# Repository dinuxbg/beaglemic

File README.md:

# BeagleMic 16-channel PDM Audio Capture

# Introduction
Ever wanted to record audio from 16 PDM microphones simultanously? Now you can with a BeagleMic running on a [PocketBeagle2](https://www.beagleboard.org/boards/pocketbeagle-2).

Yes, you could opt for the much simpler I2S microphones. But then you won't have fun writing assembly to capture and process sixteen digital signals at more than 2MHz sample rate.

Audio can be routed to BeagleBone's USB gadget driver. Multichannel audio data can be recorded from a regular PC just as you would record from any other USB microphone. See the section about Buildroot image below.

Current firmware supports:

| Feature                    | 16 Channel Mode   | 8 Channel Mode    |
|----------------------------|-------------------|-------------------|
| PDM Bit Clock              | 3.083 MHz         | 3,083 MHz         |
| PCM Output Bits Per Sample | 16 bps            | 24 bps            |
| PCM Output Sample Rate     | 24088 Samples/sec | 24088 Samples/sec |

# Freedom
To the best of my knowledge, the entire HW design is Open Hardware and designed with the libre KiCad software. The entire firmware stack is almost free software, and is built by free toolchains. The only exception are some bootloader blobs for the AM62x SoC.

Please report any closed components you notice.

# Hardware
The schematic is simple. PDM microphones' digital outputs are connected directly to the PRU input pins. The PRU also drives the bit clock. I have tested on PocketBeagle and BeagleBone AI.

| PocketBeagle | PRU Pin | Type  | Signal               |
|--------------|---------|-------|----------------------|
| P2.24        | R30_14  | Output| PDM Bit Clock        |
| P1.36        | R31_0   | Input | MIC0 and MIC1 Data   |
| P1.33        | R31_1   | Input | MIC2 and MIC3 Data   |
| P2.32        | R31_2   | Input | MIC4 and MIC5 Data   |
| P2.30        | R31_3   | Input | MIC6 and MIC7 Data   |
| P1.31        | R31_4   | Input | MIC8 and MIC9 Data   |
| P2.34        | R31_5   | Input | MIC10 and MIC11 Data |
| P2.28        | R31_6   | Input | MIC12 and MIC13 Data |
| P1.29        | R31_7   | Input | MIC14 and MIC15 Data |

Optionally, high-level software may visualize detected audio direction using a stripe of 16 LEDs hooked to two 74HC595 shift registers:

| PocketBeagle | PB GPIO  | BBAI  | BBAI GPIO | Signal |
|--------------|----------|-------|-----------|--------|
| P2.25        | gpio2_9  | P9.30 | gpio5_12  | DS     |
| P2.29        | gpio1_7  | P9.28 | gpio4_17  | SHCP   |
| P2.31        | gpio1_19 | P9.23 | gpio7_11  | STCP   |

For each microphone pair, one microphone is configured to output data on the rising clock edge, and the other is configured to output data on the falling edge. This way we need only 8 input GPIOs to capture data from all 16 microphones.

Microphone breakout board and a PocketBeagle2 Cape are provided in KiCad format.

Unfortunately the breakout board is essential for a home DIY user like me, since all PDM microphones I could find are BGA. There are numerous youtube guides how to solder BGAs at home using a skillet or a toaster oven.

# Software

PRU0 takes care of driving the PDM bit clock and capturing the microphone bit data. It then runs a CIC filter to convert PDM to PCM, and feeds PCM data to PRU1.

PRU0 has two alternative modes of operation. For 16 channels it executes 2 integrator and 2 comb stages for CIC filtering. Whereas for 8 channels it does 3.

PRU1 is retransmitting PCM data from PRU0 down to the ARM host. RPMSG is used for control commands. Shared DDRAM buffers are used for audio data.

Host audio driver presents a standard ALSA audio card, so that arecord and other standard tools can be readily used.

# Running The Example on PocketBeagle2

    # Build kernel module
    sudo apt update
    sudo apt install build-essential linux-headers-`uname -r`
    cd driver
    make
    # Install kernel module
    sudo cp beaglemic.ko /lib/modules/`uname -r`/kernel/drivers/rpmsg/
    sudo depmod -a

    # Load the driver
    sudo modprobe beaglemic

    # Build PRU firmware
    cd pru
    make
    # Start the new PRU firmware
    sudo ./start.sh

    # Record audio
    arecord  -r31888  -c16 -f S16_LE -t wav out.wav
    arecord  -r26940  -c8 -f S32_LE -t wav out.wav
    # Hit Ctrl+C to stop.

# Folder Structure

 * beaglemic-cape - Universal cape for BeagleBone AI, PocketBeagle, PocketBeagle2 and iCE40HX8K-EVB.
 * driver - Host ALSA audio driver.
 * inmp621-breakout - INMP621 Microphone breakout. Designed to be optionally used with beaglemic-cape.
 * libs - Library code. Currently contains code to drive LED ring for beaglemic-cape.
 * pru - PRU firmware.

# Further Work
A few ideas to improve the design:

 * Move comb filters to PRU1, and try to add more integrators in PRU0.
 * Clean-up the cape PCB.
   * If possible, leave headers for Class-D output from spare PRUs.
 * Migrate to latest kernel 6.??.

# Buildroot Image With USB UAC2 Gadget Mode
The above installation and build instruction steps can be daunting. A [buildroot](https://buildroot.org) configuration for PocketBeagle2 is available to automate them, and add a bit more.

The buildroot image is small (about 6MB). It initializes the BeagleMic audio driver, and links it to the UAC2 USB Gadget driver. Your BeagleMic PocketBeagle2 is presented as USB multichannel microphone, so that a regular PC can capture and run desired audio algorithms.

You need to download the beaglemic and buildroot.org GIT trees in separate directories. Then, when building from the buildroot directory you need to provide the beaglemic path via BR2_EXTERNAL environment variable. Example commands:

	git clone --depth=1 git://git.busybox.net/buildroot
	git clone --depth=1 https://gitlab.com/dinuxbg/beaglemic

	cd buildroot
	git checkout 2021.05.3  # Last BR release with kernel 4.19
	export BR2_EXTERNAL=`realpath ../beaglemic/buildroot/`
	make beaglemic_pb2_defconfig
	make -j`nproc`

Above should result in a small SDCard image which you can flash. Be sure to get the /dev/sdX right for your SD/MMC card reader.

	sudo dd if=output/images/sdcard.img of=/dev/sdX

When PocketBeagle2 boots and you connect it via USB to your host, you should be able to record:

	arecord -D hw:CARD=BeagleMic -c8 -t wav -f S32_LE -r24000 out-8ch.wav

## Audio Mode Configuration
Right now UAC2 Gadget is configured only for 8ch/32bps/24000kHz. With a few manual tweaks in buildroot/package/beaglemic-firmware/beaglemicd it can be switched to 16ch/16bps mode. I'm currently researching how I can make this configuration run-time, and how I can control the LED ring via USB.

# References
 * [CIC Filter Introduction](https://dspguru.com/dsp/tutorials/cic-filter-introduction/)
 * [Another CIC Filter Article](http://www.tsdconseil.fr/log/scriptscilab/cic/cic-en.pdf)
 * [Series of PDM articles and software implementations](https://curiouser.cheshireeng.com/category/projects/pdm-microphone-toys/)
 * [Another CIC Filter Article](https://www.embedded.com/design/configurable-systems/4006446/Understanding-cascaded-integrator-comb-filters)
 * [CIC Filter Introduction](http://home.mit.bme.hu/~kollar/papers/cic.pdf)
 * [SPM0423HD4H Datasheet](http://media.digikey.com/PDF/Data%20Sheets/Knowles%20Acoustics%20PDFs/SPM0423HD4H-WB.pdf)
 * [INMP621 Datasheet](https://invensense.tdk.com/download-pdf/inmp621-datasheet/)
 * [Inspiration for high-bandwidth data acquisition](https://github.com/ZeekHuge/BeagleScope)

# Other Resources
Below are various other CIC implementations and PDM microphone boards I've stumbled upon.
 * https://github.com/introlab/16SoundsUSB
 * https://github.com/mkj/pru-mic
 * https://github.com/introlab/odas
 * https://respeaker.io/make_a_smart_speaker/
 * https://github.com/Scrashdown/PRU-Audio-Processing
 * https://github.com/fakufaku/kurodako

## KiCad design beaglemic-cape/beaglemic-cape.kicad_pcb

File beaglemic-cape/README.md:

# Beaglemic-Cape

This is a KiCAD project for a 16 PDM Microphone board with host support for:
 * BeagleBone AI
 * PocketBeagle
 * ICE40HX8K-EVB1 (**untested!**)

PDM microphones can either be:
 * Soldered on the cape board, which is not for beginners. You would require a steady hand or pick-and-place machine, and reflow soldering oven.
 * Connected via regular headers using external [breakout](../inmp621-breakout/README.md) [board](https://www.adafruit.com/product/3492).

# Future Improvements

A few ideas for improvements in an eventual future PCB revision:

 * Move the USB OTG connector to the outer edge, so that cable does not interfere with PocketBeagle.
 * Add a few extra LEDs for power and other status.
 * Add better package placement indicators on silkscreen (e.g. first pin, IC dent).
 * Remove the BBAI connector. I couldn't find a way to utilize the proprietary DSPs, so let's focus on USB microphone with PocketBeagle.
 * Switch to bottom-facing LEDs so that all SMD parts are on one of the PCB sides.

# References
 * Microphone footprint, 3D model and schematics symbol are taken from https://www.snapeda.com/parts/INMP621/InvenSense/view-part/?ref=digikey . Footprint has minor modification to "break" the ground track and ease the data wires routing.
 * Freerouting.org was used for routing some of the PCB tracks.

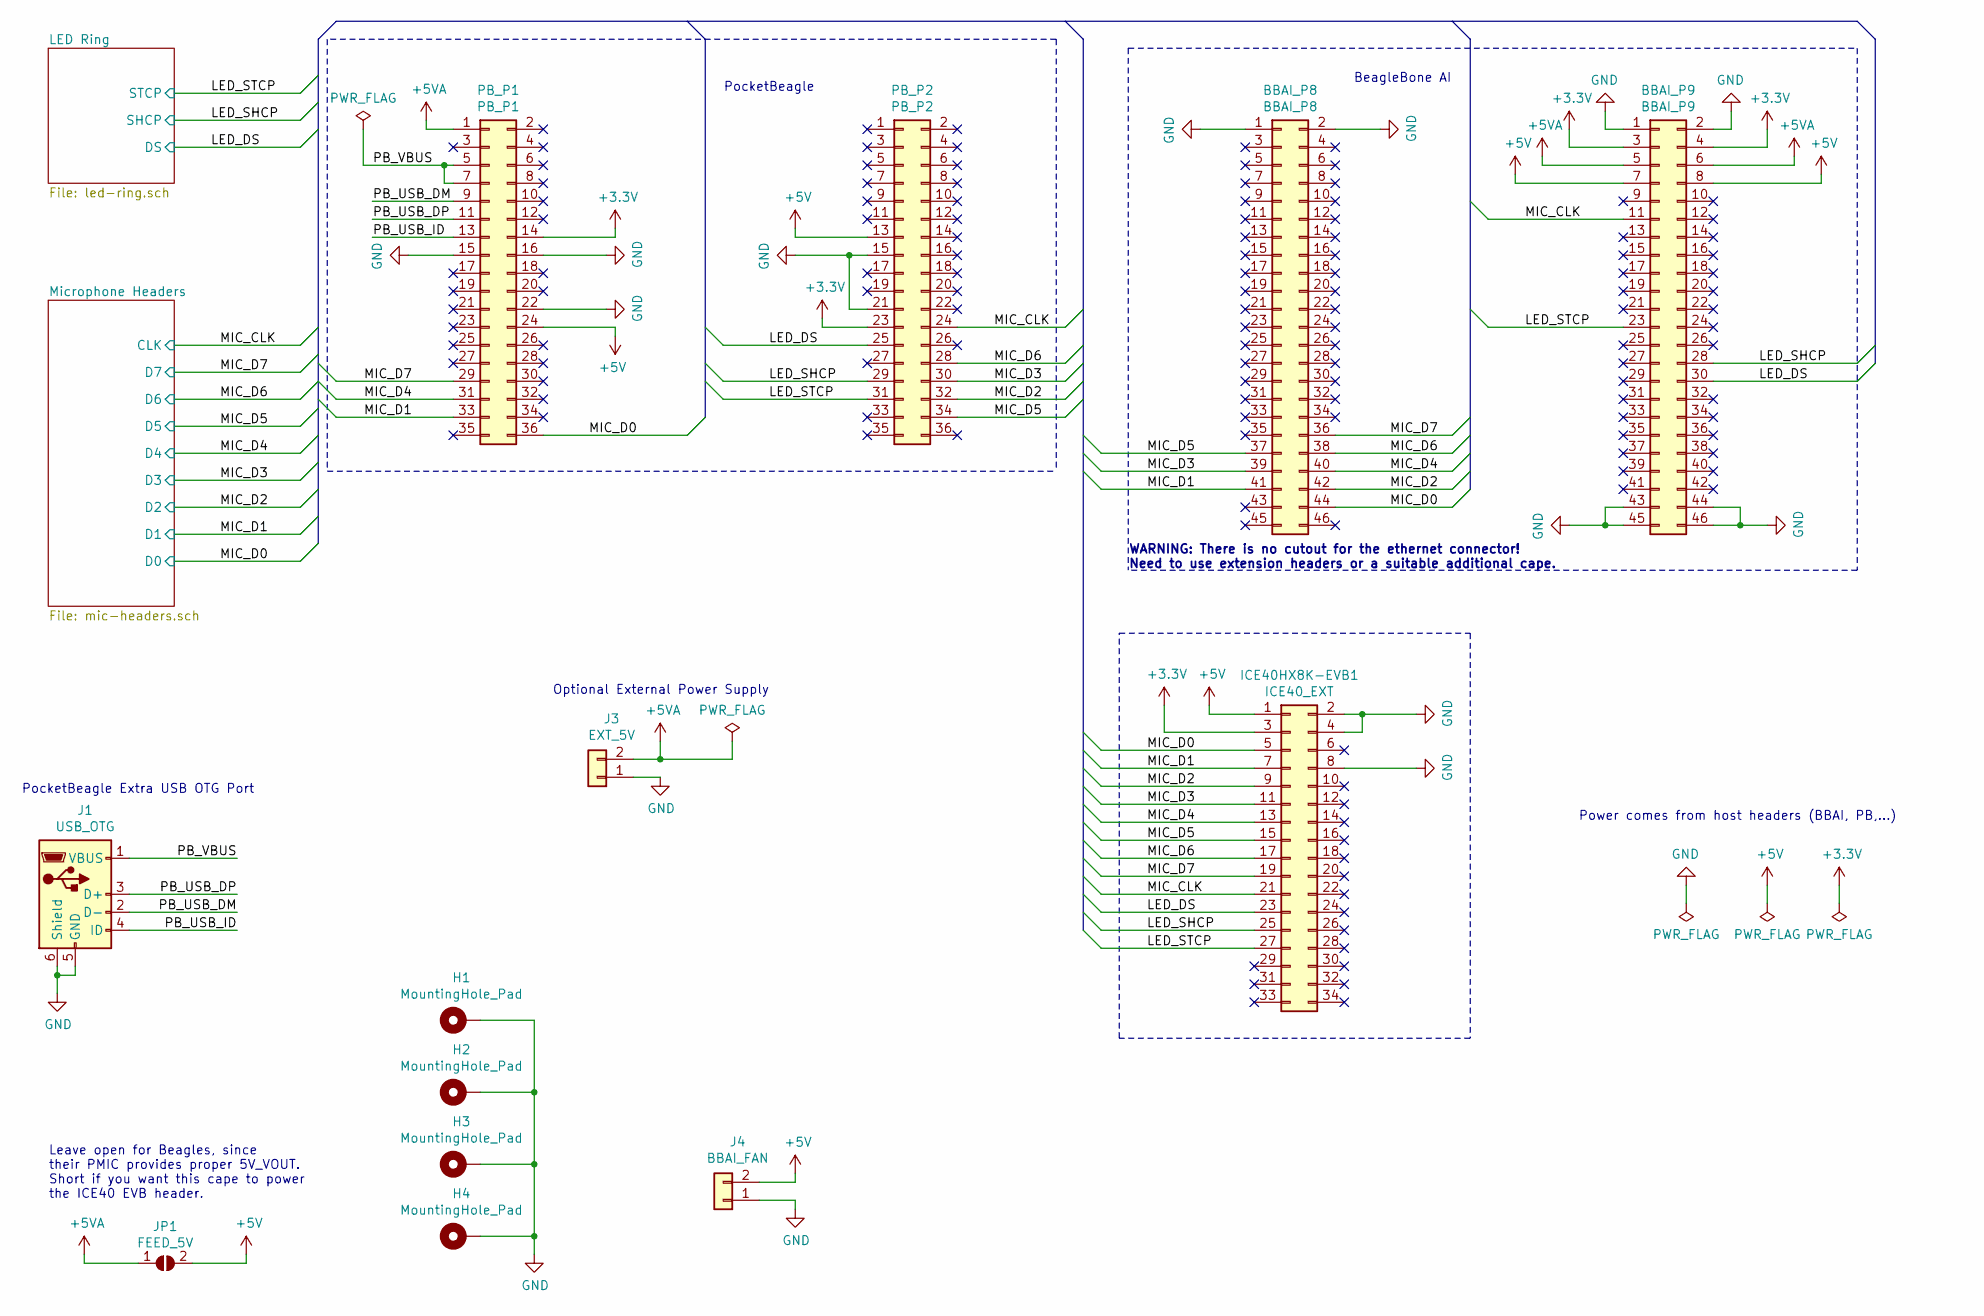
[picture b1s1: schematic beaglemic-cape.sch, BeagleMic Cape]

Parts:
BBAI_P8: BBAI_P8; PinSocket_2x23_P2.54mm_Vertical
BBAI_P9: BBAI_P9; PinSocket_2x23_P2.54mm_Vertical
H1, H2, H3, H4: MountingHole_Pad; MountingHole_3.2mm_M3_ISO14580_Pad
ICE40HX8K-EVB1: ICE40_EXT; PinSocket_2x17_P2.54mm_Vertical
J1: USB_OTG; USB_Micro-B_Tensility_54-00023_Vertical_CircularHoles
J3: EXT_5V; PinHeader_1x02_P2.54mm_Vertical
J4: BBAI_FAN; PinHeader_1x02_P2.54mm_Vertical
JP1: FEED_5V; SolderJumper-2_P1.3mm_Open_RoundedPad1.0x1.5mm
PB_P1: PB_P1; PinHeader_2x18_P2.54mm_Vertical
PB_P2: PB_P2; PinHeader_2x18_P2.54mm_Vertical

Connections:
+3V3: BBAI_P9.3, BBAI_P9.4, ICE40HX8K-EVB1.3, PB_P1.14, PB_P2.23; also elsewhere on the board
+5V: BBAI_P9.7, BBAI_P9.8, ICE40HX8K-EVB1.1, J4.2, JP1.2 (B), PB_P1.24, PB_P2.13; also elsewhere on the board
+5VA: BBAI_P9.5, BBAI_P9.6, J3.2, JP1.1 (A), PB_P1.1
/LED_DS: BBAI_P9.30, ICE40HX8K-EVB1.23, PB_P2.25; also elsewhere on the board
/LED_SHCP: BBAI_P9.28, ICE40HX8K-EVB1.25, PB_P2.29; also elsewhere on the board
/LED_STCP: BBAI_P9.23, ICE40HX8K-EVB1.27, PB_P2.31; also elsewhere on the board
/MIC_CLK: BBAI_P9.11, ICE40HX8K-EVB1.21, PB_P2.24; also elsewhere on the board
/MIC_D0: BBAI_P8.44, ICE40HX8K-EVB1.5, PB_P1.36; also elsewhere on the board
/MIC_D1: BBAI_P8.41, ICE40HX8K-EVB1.7, PB_P1.33; also elsewhere on the board
/MIC_D2: BBAI_P8.42, ICE40HX8K-EVB1.9, PB_P2.32; also elsewhere on the board
/MIC_D3: BBAI_P8.39, ICE40HX8K-EVB1.11, PB_P2.30; also elsewhere on the board
/MIC_D4: BBAI_P8.40, ICE40HX8K-EVB1.13, PB_P1.31; also elsewhere on the board
/MIC_D5: BBAI_P8.37, ICE40HX8K-EVB1.15, PB_P2.34; also elsewhere on the board
/MIC_D6: BBAI_P8.38, ICE40HX8K-EVB1.17, PB_P2.28; also elsewhere on the board
/MIC_D7: BBAI_P8.36, ICE40HX8K-EVB1.19, PB_P1.29; also elsewhere on the board
/PB_USB_DM: J1.2 (D-), PB_P1.9
/PB_USB_DP: J1.3 (D+), PB_P1.11
/PB_USB_ID: J1.4 (ID), PB_P1.13
/PB_VBUS: J1.1 (VBUS), PB_P1.5, PB_P1.7
GND: BBAI_P8.1, BBAI_P8.2, BBAI_P9.1, BBAI_P9.2, BBAI_P9.43, BBAI_P9.44, BBAI_P9.45, BBAI_P9.46, H1.1, H2.1, H3.1, H4.1, ICE40HX8K-EVB1.2, ICE40HX8K-EVB1.4, ICE40HX8K-EVB1.8, J1.5 (GND), J1.6 (Shield), J3.1, J4.1, PB_P1.15, PB_P1.16, PB_P1.22, PB_P2.15, PB_P2.21; also elsewhere on the board

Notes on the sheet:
Power comes from host headers (BBAI, PB,...)
PocketBeagle Extra USB OTG Port
Optional External Power Supply
Leave open for Beagles, since their PMIC provides proper 5V_VOUT. Short if you want this cape to power the ICE40 EVB header.
PocketBeagle
BeagleBone AI
WARNING: There is no cutout for the ethernet connector! Need to use extension headers or a suitable additional cape.

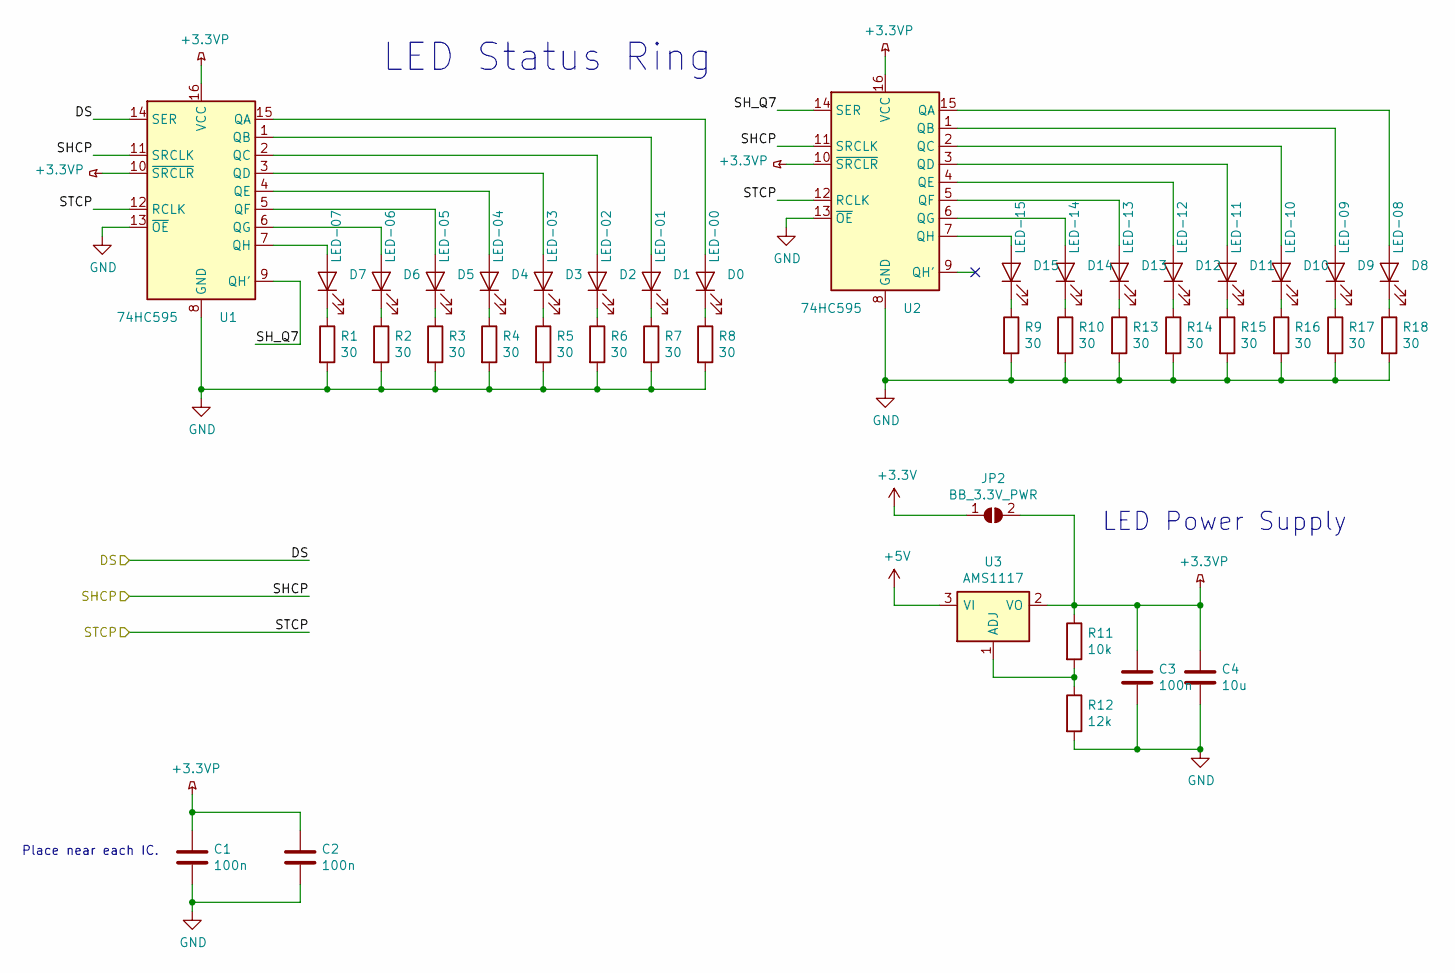
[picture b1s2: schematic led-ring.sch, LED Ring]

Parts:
C1, C2, C3: 100n; C_0805_2012Metric
C4: 10u; C_0805_2012Metric
D0: LED-00; LED_0805_2012Metric
D1: LED-01; LED_0805_2012Metric
D2: LED-02; LED_0805_2012Metric
D3: LED-03; LED_0805_2012Metric
D4: LED-04; LED_0805_2012Metric
D5: LED-05; LED_0805_2012Metric
D6: LED-06; LED_0805_2012Metric
D7: LED-07; LED_0805_2012Metric
D8: LED-08; LED_0805_2012Metric
D9: LED-09; LED_0805_2012Metric
D10: LED-10; LED_0805_2012Metric
D11: LED-11; LED_0805_2012Metric
D12: LED-12; LED_0805_2012Metric
D13: LED-13; LED_0805_2012Metric
D14: LED-14; LED_0805_2012Metric
D15: LED-15; LED_0805_2012Metric
JP2: BB_3.3V_PWR; SolderJumper-2_P1.3mm_Open_RoundedPad1.0x1.5mm
R1, R2, R3, R4, R5, R6, R7, R8, R9, R10, R13, R14, R15, R16, R17, R18: 30; R_0805_2012Metric
R11: 10k; R_0805_2012Metric
R12: 12k; R_0805_2012Metric
U1, U2: 74HC595; TSSOP-16_4.4x5mm_P0.65mm
U3: AMS1117; SOT-223-3_TabPin2

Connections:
+3.3VP: C1.1, C2.1, C3.1, C4.1, JP2.2 (B), R11.1, U1.10 (~SRCLR), U1.16 (VCC), U2.10 (~SRCLR), U2.16 (VCC), U3.2 (VO)
+3V3: JP2.1 (A); also elsewhere on the board
+5V: U3.3 (VI); also elsewhere on the board
/LED Ring/SH_Q7: U1.9 (QH'), U2.14 (SER)
/LED_DS: U1.14 (SER); also elsewhere on the board
/LED_SHCP: U1.11 (SRCLK), U2.11 (SRCLK); also elsewhere on the board
/LED_STCP: U1.12 (RCLK), U2.12 (RCLK); also elsewhere on the board
GND: C1.2, C2.2, C3.2, C4.2, R1.2, R2.2, R3.2, R4.2, R5.2, R6.2, R7.2, R8.2, R9.2, R10.2, R12.2, R13.2, R14.2, R15.2, R16.2, R17.2, R18.2, U1.8 (GND), U1.13 (~OE), U2.8 (GND), U2.13 (~OE); also elsewhere on the board
unnamed: D0.1 (K), R8.1
unnamed: D0.2 (A), U1.15 (QA)
unnamed: D1.1 (K), R7.1
unnamed: D1.2 (A), U1.1 (QB)
unnamed: D2.1 (K), R6.1
unnamed: D2.2 (A), U1.2 (QC)
unnamed: D3.1 (K), R5.1
unnamed: D3.2 (A), U1.3 (QD)
unnamed: D4.1 (K), R4.1
unnamed: D4.2 (A), U1.4 (QE)
unnamed: D5.1 (K), R3.1
unnamed: D5.2 (A), U1.5 (QF)
unnamed: D6.1 (K), R2.1
unnamed: D6.2 (A), U1.6 (QG)
unnamed: D7.1 (K), R1.1
unnamed: D7.2 (A), U1.7 (QH)
unnamed: D8.1 (K), R18.1
unnamed: D8.2 (A), U2.15 (QA)
unnamed: D9.1 (K), R17.1
unnamed: D9.2 (A), U2.1 (QB)
unnamed: D10.1 (K), R16.1
unnamed: D10.2 (A), U2.2 (QC)
unnamed: D11.1 (K), R15.1
unnamed: D11.2 (A), U2.3 (QD)
unnamed: D12.1 (K), R14.1
unnamed: D12.2 (A), U2.4 (QE)
unnamed: D13.1 (K), R13.1
unnamed: D13.2 (A), U2.5 (QF)
unnamed: D14.1 (K), R10.1
unnamed: D14.2 (A), U2.6 (QG)
unnamed: D15.1 (K), R9.1
unnamed: D15.2 (A), U2.7 (QH)
unnamed: R11.2, R12.1, U3.1 (ADJ)

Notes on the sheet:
LED Status Ring
LED Power Supply
Place near each IC.

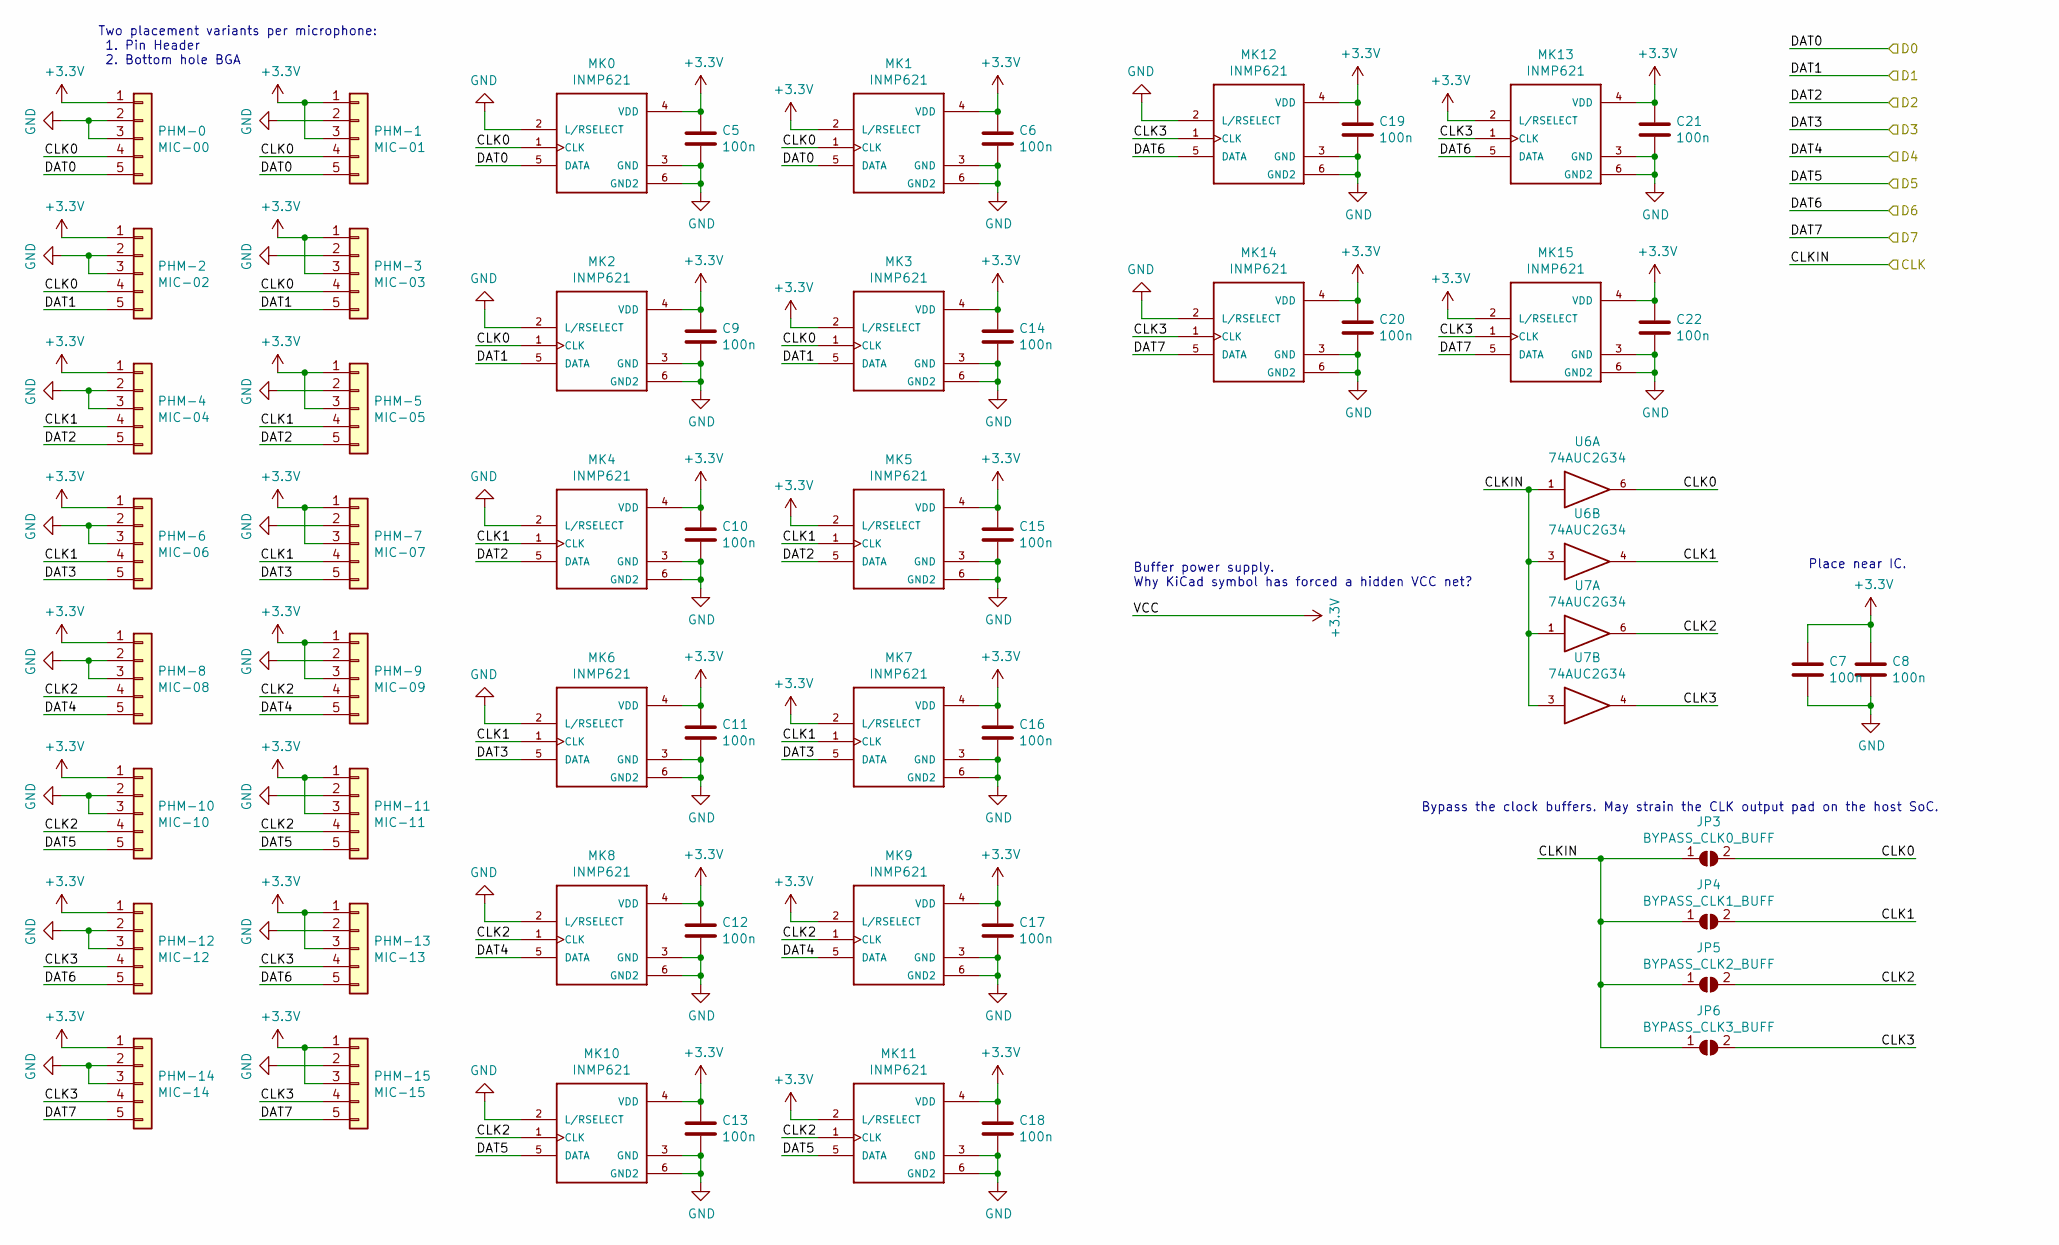
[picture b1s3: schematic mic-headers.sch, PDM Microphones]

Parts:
C5, C6, C7, C8, C9, C10, C11, C12, C13, C14, C15, C16, C17, C18, C19, C20, C21, C22: 100n; C_0805_2012Metric
JP3: BYPASS_CLK0_BUFF; SolderJumper-2_P1.3mm_Open_RoundedPad1.0x1.5mm
JP4: BYPASS_CLK1_BUFF; SolderJumper-2_P1.3mm_Open_RoundedPad1.0x1.5mm
JP5: BYPASS_CLK2_BUFF; SolderJumper-2_P1.3mm_Open_RoundedPad1.0x1.5mm
JP6: BYPASS_CLK3_BUFF; SolderJumper-2_P1.3mm_Open_RoundedPad1.0x1.5mm
MK0, MK1, MK2, MK3, MK4, MK5, MK6, MK7, MK8, MK9, MK10, MK11, MK12, MK13, MK14, MK15: INMP621; MK_INMP621
PHM-0: MIC-00; PinSocket_1x05_P2.54mm_Vertical
PHM-1: MIC-01; PinSocket_1x05_P2.54mm_Vertical
PHM-2: MIC-02; PinSocket_1x05_P2.54mm_Vertical
PHM-3: MIC-03; PinSocket_1x05_P2.54mm_Vertical
PHM-4: MIC-04; PinSocket_1x05_P2.54mm_Vertical
PHM-5: MIC-05; PinSocket_1x05_P2.54mm_Vertical
PHM-6: MIC-06; PinSocket_1x05_P2.54mm_Vertical
PHM-7: MIC-07; PinSocket_1x05_P2.54mm_Vertical
PHM-8: MIC-08; PinSocket_1x05_P2.54mm_Vertical
PHM-9: MIC-09; PinSocket_1x05_P2.54mm_Vertical
PHM-10: MIC-10; PinSocket_1x05_P2.54mm_Vertical
PHM-11: MIC-11; PinSocket_1x05_P2.54mm_Vertical
PHM-12: MIC-12; PinSocket_1x05_P2.54mm_Vertical
PHM-13: MIC-13; PinSocket_1x05_P2.54mm_Vertical
PHM-14: MIC-14; PinSocket_1x05_P2.54mm_Vertical
PHM-15: MIC-15; PinSocket_1x05_P2.54mm_Vertical
U6, U7: 74AUC2G34; SOT-23-6

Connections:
+3V3: C5.1, C6.1, C7.1, C8.1, C9.1, C10.1, C11.1, C12.1, C13.1, C14.1, C15.1, C16.1, C17.1, C18.1, C19.1, C20.1, C21.1, C22.1, MK0.4 (VDD), MK1.2 (L/RSELECT), MK1.4 (VDD), MK2.4 (VDD), MK3.2 (L/RSELECT), MK3.4 (VDD), MK4.4 (VDD), MK5.2 (L/RSELECT), MK5.4 (VDD), MK6.4 (VDD), MK7.2 (L/RSELECT), MK7.4 (VDD), MK8.4 (VDD), MK9.2 (L/RSELECT), MK9.4 (VDD), MK10.4 (VDD), MK11.2 (L/RSELECT), MK11.4 (VDD), MK12.4 (VDD), MK13.2 (L/RSELECT), MK13.4 (VDD), MK14.4 (VDD), MK15.2 (L/RSELECT), MK15.4 (VDD), PHM-0.1, PHM-1.1, PHM-1.3, PHM-2.1, PHM-3.1, PHM-3.3, PHM-4.1, PHM-5.1, PHM-5.3, PHM-6.1, PHM-7.1, PHM-7.3, PHM-8.1, PHM-9.1, PHM-9.3, PHM-10.1, PHM-11.1, PHM-11.3, PHM-12.1, PHM-13.1, PHM-13.3, PHM-14.1, PHM-15.1, PHM-15.3, U6.5 (VCC), U7.5 (VCC); also elsewhere on the board
/MIC_CLK: JP3.1 (A), JP4.1 (A), JP5.1 (A), JP6.1 (A), U6.1, U6.3, U7.1, U7.3; also elsewhere on the board
/MIC_D0: MK0.5 (DATA), MK1.5 (DATA), PHM-0.5, PHM-1.5; also elsewhere on the board
/MIC_D1: MK2.5 (DATA), MK3.5 (DATA), PHM-2.5, PHM-3.5; also elsewhere on the board
/MIC_D2: MK4.5 (DATA), MK5.5 (DATA), PHM-4.5, PHM-5.5; also elsewhere on the board
/MIC_D3: MK6.5 (DATA), MK7.5 (DATA), PHM-6.5, PHM-7.5; also elsewhere on the board
/MIC_D4: MK8.5 (DATA), MK9.5 (DATA), PHM-8.5, PHM-9.5; also elsewhere on the board
/MIC_D5: MK10.5 (DATA), MK11.5 (DATA), PHM-10.5, PHM-11.5; also elsewhere on the board
/MIC_D6: MK12.5 (DATA), MK13.5 (DATA), PHM-12.5, PHM-13.5; also elsewhere on the board
/MIC_D7: MK14.5 (DATA), MK15.5 (DATA), PHM-14.5, PHM-15.5; also elsewhere on the board
/Microphone Headers/CLK0: JP3.2 (B), MK0.1 (CLK), MK1.1 (CLK), MK2.1 (CLK), MK3.1 (CLK), PHM-0.4, PHM-1.4, PHM-2.4, PHM-3.4, U6.6
/Microphone Headers/CLK1: JP4.2 (B), MK4.1 (CLK), MK5.1 (CLK), MK6.1 (CLK), MK7.1 (CLK), PHM-4.4, PHM-5.4, PHM-6.4, PHM-7.4, U6.4
/Microphone Headers/CLK2: JP5.2 (B), MK8.1 (CLK), MK9.1 (CLK), MK10.1 (CLK), MK11.1 (CLK), PHM-8.4, PHM-9.4, PHM-10.4, PHM-11.4, U7.6
/Microphone Headers/CLK3: JP6.2 (B), MK12.1 (CLK), MK13.1 (CLK), MK14.1 (CLK), MK15.1 (CLK), PHM-12.4, PHM-13.4, PHM-14.4, PHM-15.4, U7.4
GND: C5.2, C6.2, C7.2, C8.2, C9.2, C10.2, C11.2, C12.2, C13.2, C14.2, C15.2, C16.2, C17.2, C18.2, C19.2, C20.2, C21.2, C22.2, MK0.2 (L/RSELECT), MK0.3 (GND), MK0.6 (GND2), MK1.3 (GND), MK1.6 (GND2), MK2.2 (L/RSELECT), MK2.3 (GND), MK2.6 (GND2), MK3.3 (GND), MK3.6 (GND2), MK4.2 (L/RSELECT), MK4.3 (GND), MK4.6 (GND2), MK5.3 (GND), MK5.6 (GND2), MK6.2 (L/RSELECT), MK6.3 (GND), MK6.6 (GND2), MK7.3 (GND), MK7.6 (GND2), MK8.2 (L/RSELECT), MK8.3 (GND), MK8.6 (GND2), MK9.3 (GND), MK9.6 (GND2), MK10.2 (L/RSELECT), MK10.3 (GND), MK10.6 (GND2), MK11.3 (GND), MK11.6 (GND2), MK12.2 (L/RSELECT), MK12.3 (GND), MK12.6 (GND2), MK13.3 (GND), MK13.6 (GND2), MK14.2 (L/RSELECT), MK14.3 (GND), MK14.6 (GND2), MK15.3 (GND), MK15.6 (GND2), PHM-0.2, PHM-0.3, PHM-1.2, PHM-2.2, PHM-2.3, PHM-3.2, PHM-4.2, PHM-4.3, PHM-5.2, PHM-6.2, PHM-6.3, PHM-7.2, PHM-8.2, PHM-8.3, PHM-9.2, PHM-10.2, PHM-10.3, PHM-11.2, PHM-12.2, PHM-12.3, PHM-13.2, PHM-14.2, PHM-14.3, PHM-15.2, U6.2 (GND), U7.2 (GND); also elsewhere on the board

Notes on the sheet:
Bypass the clock buffers. May strain the CLK output pad on the host SoC.
Place near IC.
Two placement variants per microphone: 1. Pin Header 2. Bottom hole BGA
Buffer power supply. Why KiCad symbol has forced a hidden VCC net?

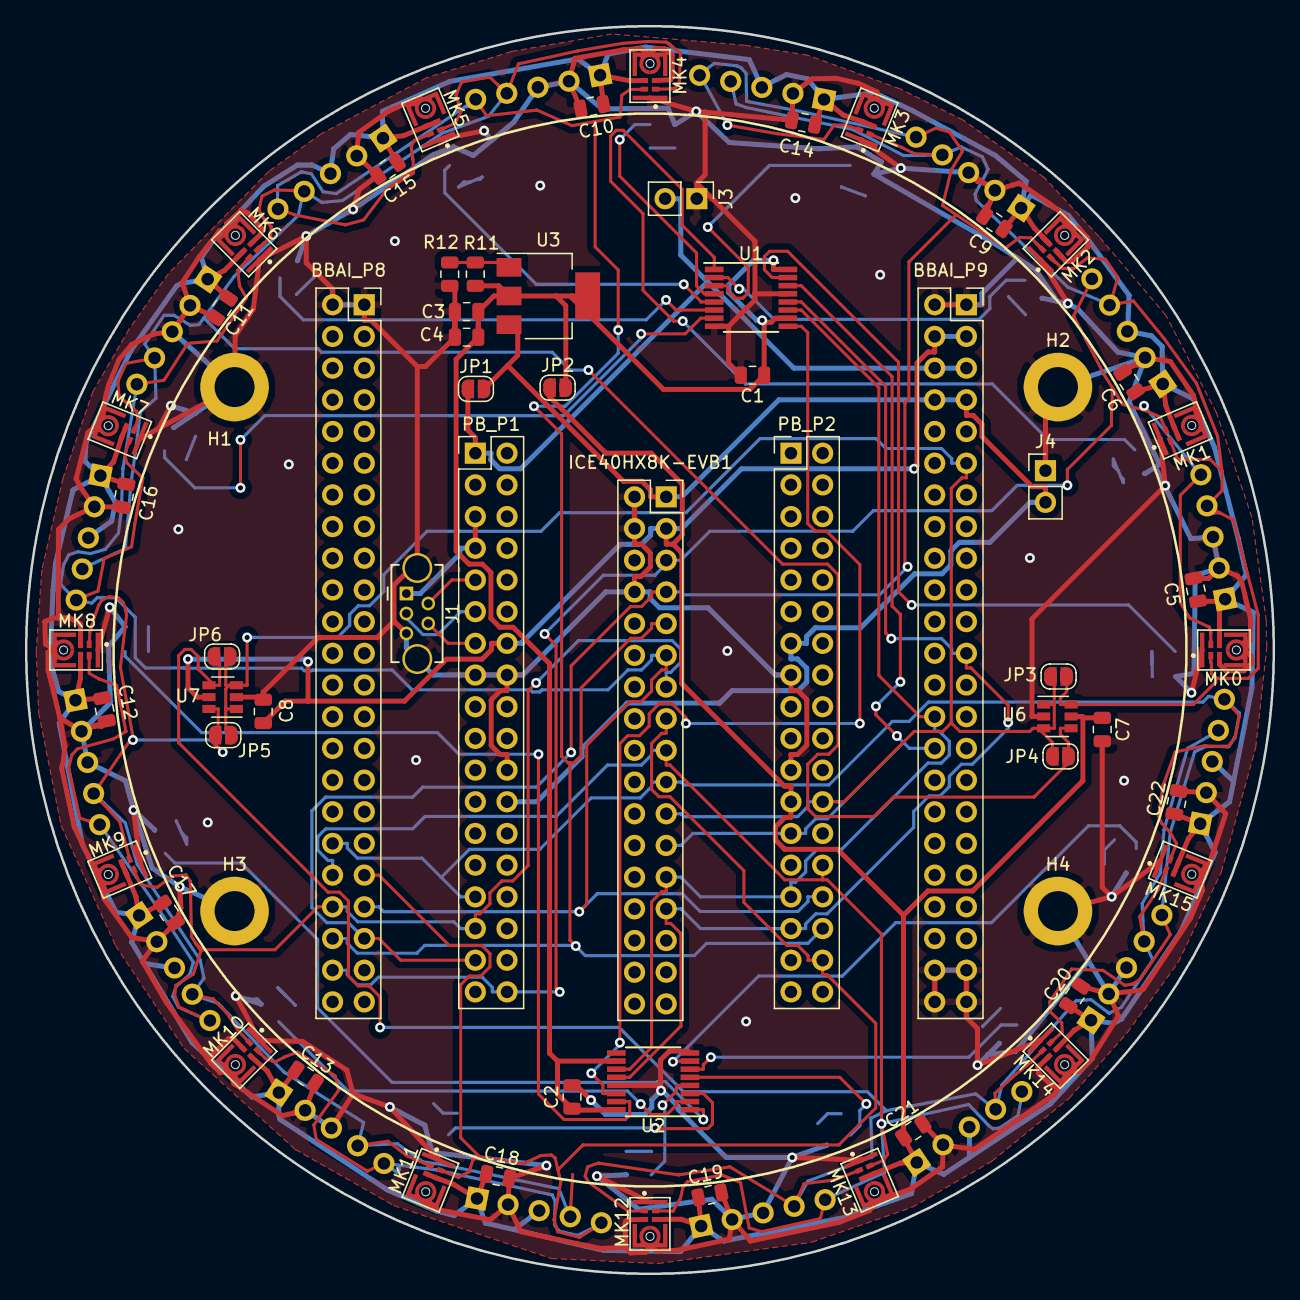
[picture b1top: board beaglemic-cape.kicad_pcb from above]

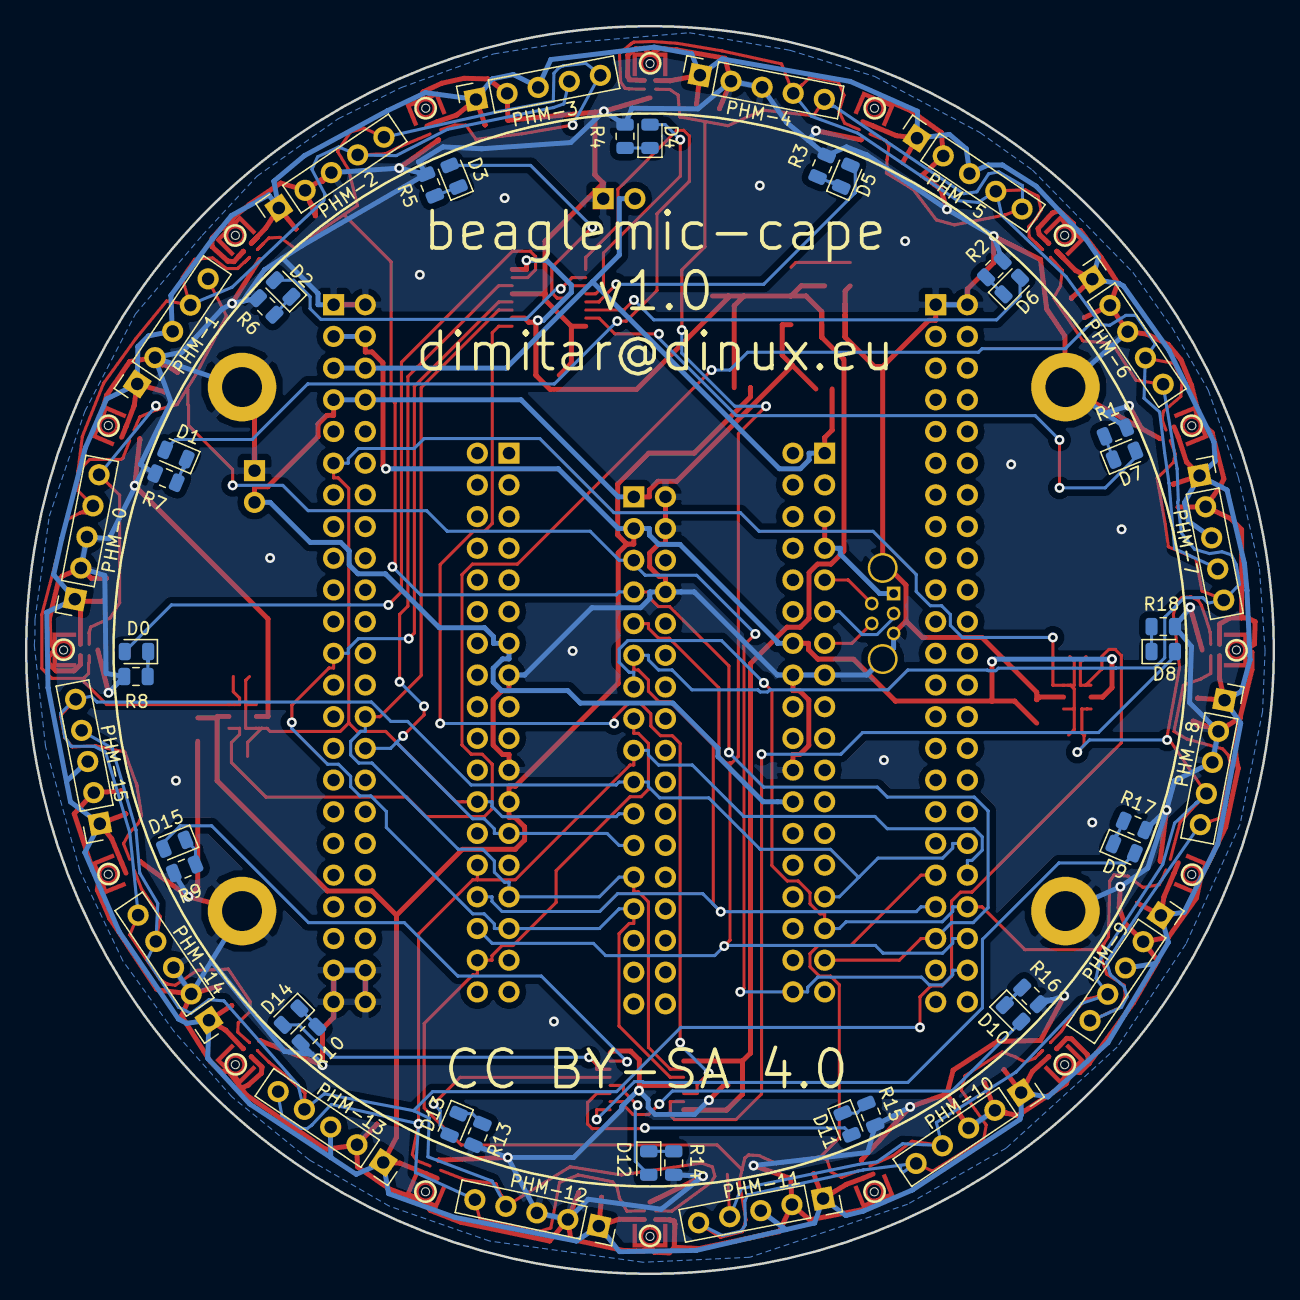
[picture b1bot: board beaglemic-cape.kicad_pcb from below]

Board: 2 copper layers, 100.0 x 100.0 mm, 111 parts (48 on the bottom side), 59 nets.

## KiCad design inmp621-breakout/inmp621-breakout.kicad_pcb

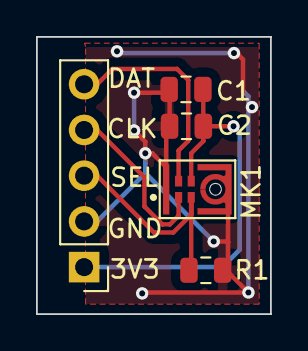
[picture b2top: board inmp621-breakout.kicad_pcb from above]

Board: 2 copper layers, 13.0 x 15.4 mm, 5 parts (0 on the bottom side), 5 nets.

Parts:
C1: 1u; C_0805_2012Metric
C2: 100n; C_0805_2012Metric
J1: Conn_01x05; PinHeader_1x05_P2.54mm_Vertical
MK1: INMP621; MK_INMP621
R1: NC; R_0805_2012Metric

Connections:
/3V3: C1.1, C2.1, J1.1, MK1.4
/CLK: J1.4, MK1.1
/DAT: J1.5, MK1.5
/GND: C1.2, C2.2, J1.2, MK1.3, MK1.6, R1.2
/SEL: J1.3, MK1.2, R1.1

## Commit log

2018-11-25 Add BeagleMic project
2019-03-19 Add beaglemic cape errata
2019-04-29 beaglemic: Add stream-stop command
    System should no longer be swamped with RPMSG errors when recording stops.
2019-09-22 beaglemic: Update documentation
    Cape and PDM breakout boards have been validated, and errata has been written.
    So update README to remove the "untested" reference.
2019-09-23 Migrate beaglemic to ALSA
2019-09-23 beaglemic: Update README to account for ALSA migration
2020-01-04 beaglemic: Add documentation for running on BBAI
2020-01-04 beaglemic: INMP621 breakout - rc1
    Initial release for the INMP621 PDM microphone breakout board.
    WARNING - I have not validated it yet!
2020-01-04 beaglemic: BeagleMic Cape - rc1
    Cape allowing to connect 16 PDM breakout boards to either:
    * PocketBeagle
    * BeagleBone AI
    * iCE40HX8K-EVB
    WARNING - I have not validated it yet!
2020-01-04 beaglemic: Additional documentation
2020-01-04 beaglemic: Validate LED strip on PocketBeagle
2020-01-06 Fix doc typo
2020-01-06 Add pocketbeagle LED strip connections
2020-01-19 beaglemic-cape: Shrink PCB to 100x100mm
    Let's keep the PCB in the hobby price range.
    Version 1.0-rc2
    TODO: Route me!
2020-01-19 Minor documentation improvements
2020-01-19 Add more resources to documentation
2020-01-23 inmp621-breakout: Minor silkscreen fixes
2020-01-26 beaglemic-cape: Route PCB
    WARNING - NOT TESTED YET!
2020-02-22 inmp621-breakout: Bump version
    PCB was validated, so set version to 1.0.
2020-02-22 Deprecate pocket-cape and spm0423hd4h-breakout
    Those designs were validated to work correctly. But they proved
    difficult to assemble due to the multiple wires. Also, fitting
    two microphones on a single PCB puts too much constraints on the
    mechanical design.
2020-03-03 Minor source cleanup
2020-03-22 Add missing shell script for BBAI
    Setup differs between PocketBeagle and BBAI:
    - PinMux can only be done from DTS on BBAI.
    - Remoteproc numbers are different.
2020-04-05 Add pinctrl config for PB led strip
2020-04-05 beaglemic-cape: Minor documentation updates
2020-04-20 Minor errata update
2020-04-26 Alternative firmware and driver for 8 channel 24-bit PCM mode
    Better results For far-field audio capture are obtained with
    more bits per sample and higher PDM clock frequency. Unfortunately
    we need to reduce number of channels from 16 down to 8 to achieve that.
2020-05-17 pru: Fix channel order
    Sampling just before rising edge is for MIC0 (grounded RSELECT).
    MIC1 is sampled on or before falling edge.
2020-05-17 Gradute from testing phase
    Cape with soldered microphones was tested on BBAI and PocketBeagle.
2020-05-18 Add software diagram
2020-05-30 Add option for either 8ch24bit or 16ch16bit mode
2020-05-30 Allow more time for PRU1 to fetch data.
2020-05-30 Add debug signal option
2020-05-30 PRU1: Always acknowledge peer interrupt
    Even if stream is disabled, let's acknowledge the peer PRU0
    interrupt.
2020-05-30 PRU0: Reset microphone when switching modes
    This fixes occasional increased noise in some channels
    when switching between 16ch and 8ch modes.
2020-05-30 Shorten the ALSA card name
2020-09-04 Add buildroot for USB UAC2 gadget mode
2020-10-11 g_uac: Add compand filter
2020-10-31 Clarify that entire project is Libre SW and Libre HW
2020-10-31 Calculate MIC placement for ODAS config file
2020-10-31 Add inmp621 breakout license
2020-10-31 Switch license of my own PRU work to BSD-2-Clause
2020-10-31 More license clarifications
2020-10-31 Remove deprecated boards
2020-11-01 buildroot: Decrease gain
2020-11-06 Add OSHW certification
2021-01-01 buildroot: Switch to simple gain
    Drop the compand operation and instead do a simple gain for the audio
    data we send over USB.
    It turned out that:
    - SOX compand (predictably) adds large latency.
    - It is difficult to tune the compand filter parameters.
    So instead let's defer this complex job to the user (e.g. ODAS).
2021-01-28 Add COPYING
    Collected using:
    find . -name COPYING -o -name LICENSE | while read L; do echo "========================== $L ==========================" >> COPYING; cat $L >> COPYING; echo "" >> COPYING; done
2021-01-28 buildroot: Add COPYING to package beaglemic-driver
2021-01-28 buildroot: Add COPYING to package beaglemic-firmware
2021-01-30 Add section about buildroot in the introduction
2021-07-06 beaglemic-cape: Add a few more TODOs
2021-09-25 Use new __R30/__R31 feature for GCC
    Requires GCC version 12 and updated gnuprumcu package.
2021-09-25 Let's try the latest source version
2021-09-25 Fix buildroot instructions
2021-09-26 regio: One more cleanup
2021-09-26 Update for buildroot
2022-05-30 Specify the buildroot release
    Also update the github download URLs, since it apparently no longer
    supports the git:// protocol.
2022-06-10 Fix image path in README
2022-06-10 README: Fix url
2023-02-10 Add ODAS configuration
2023-11-24 Add makefile for plantuml
2024-09-23 WIP: Unvalidated notes for running on BBB
2025-01-12 Add link to pru-mic
2025-01-12 Bump buildroot kernel version
2025-03-23 Port to PocketBeagle2 - WIP

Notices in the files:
beaglemic-cape/beaglemic-cape.kicad_pcb:
CC BY-SA 4.0
